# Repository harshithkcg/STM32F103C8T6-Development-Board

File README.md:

# STM32F103C8T6-Development-Board
Custom STM32F103C8T6 Development Board designed in KiCad with USB, SWD programming, UART, I2C and AMS1117 power supply.

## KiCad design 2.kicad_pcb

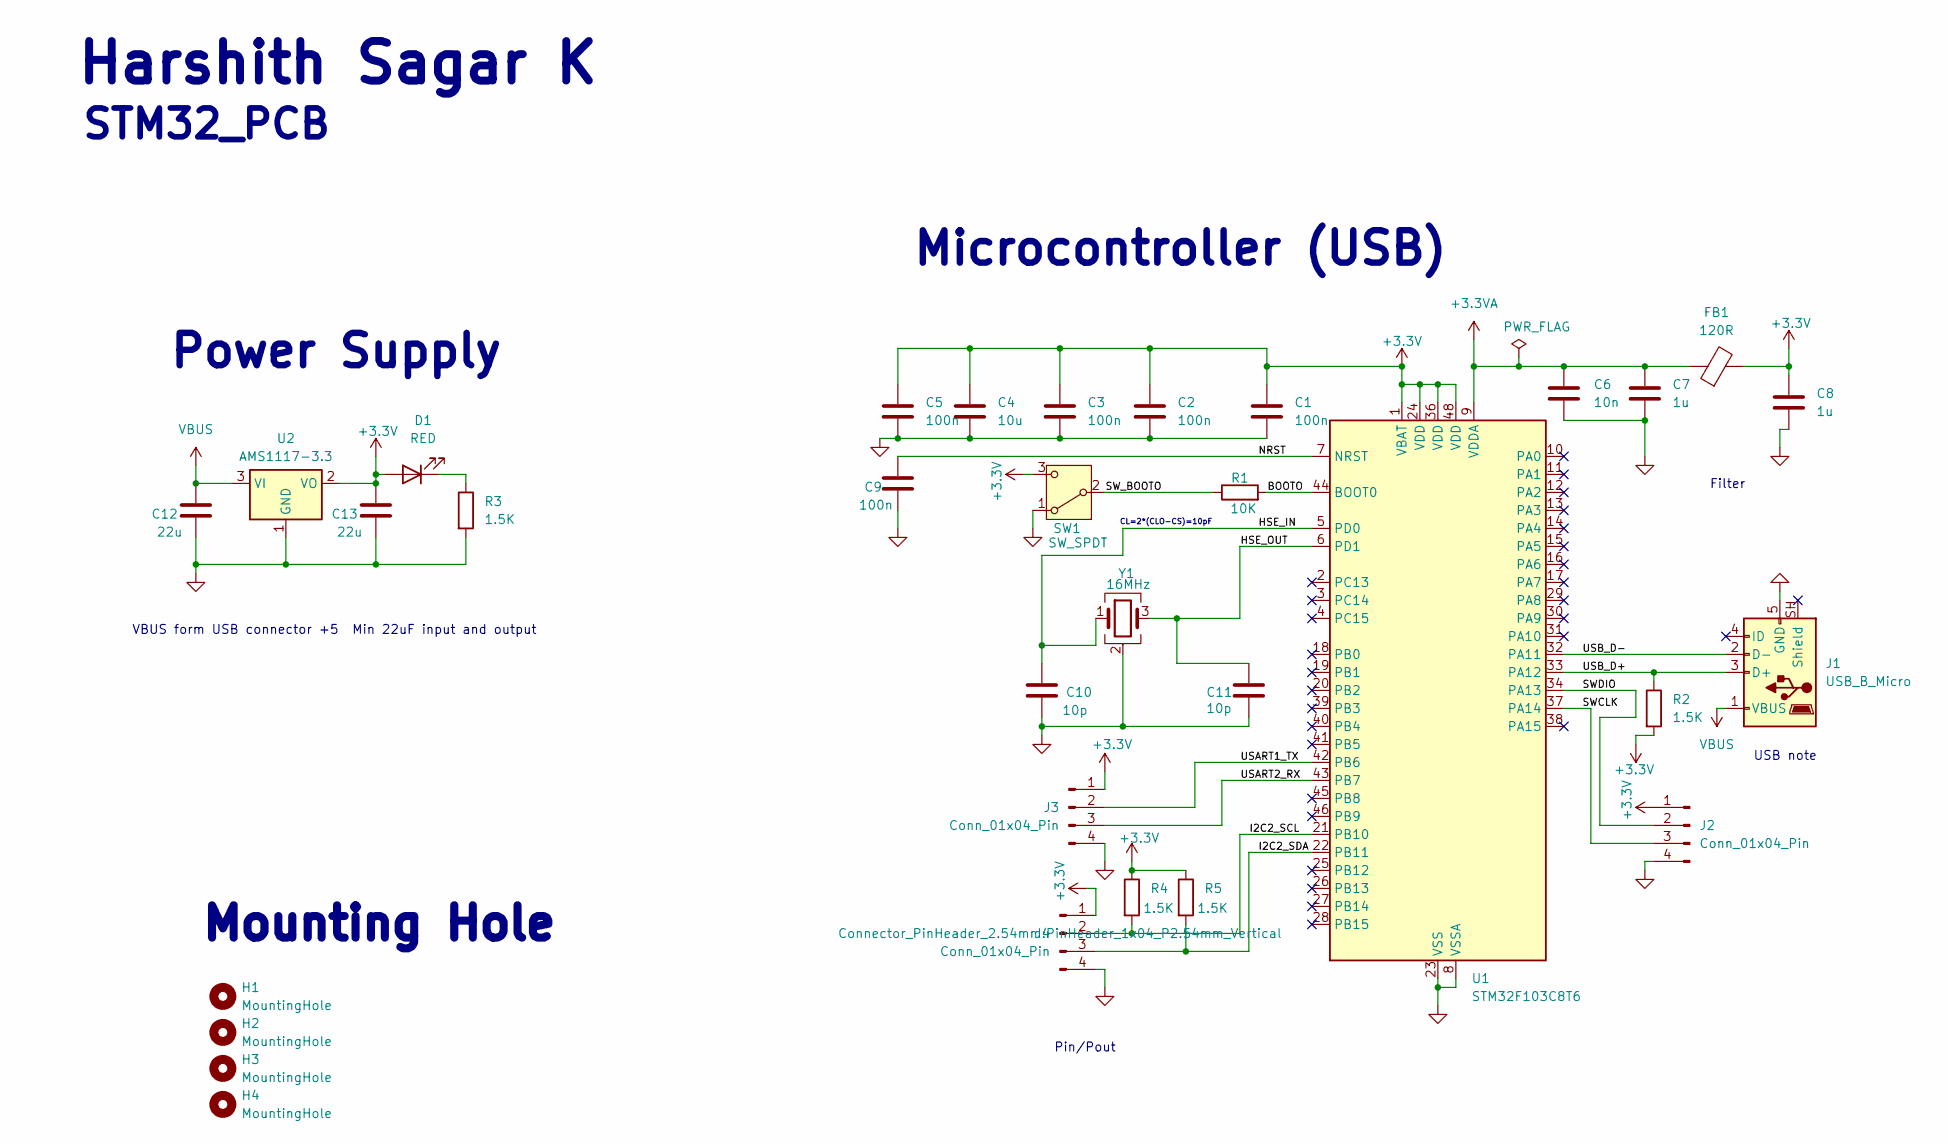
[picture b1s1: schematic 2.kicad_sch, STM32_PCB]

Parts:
C1, C2, C3, C5, C9: 100n; C_0402_1005Metric
C4: 10u; C_0603_1608Metric
C6: 10n; C_0402_1005Metric
C7, C8: 1u; C_0402_1005Metric
C10, C11: 10p; C_0402_1005Metric
C12, C13: 22u; C_0805_2012Metric
D1: RED; LED_0603_1608Metric
FB1: 120R; L_0603_1608Metric
H1, H2, H3, H4: MountingHole; MountingHole_2.1mm
J1: USB_B_Micro; USB_Micro-B_Wuerth_629105150521
J2, J3, J4: Conn_01x04_Pin; PinHeader_1x04_P2.54mm_Vertical
R1: 10K; R_0402_1005Metric
R2, R3, R4, R5: 1.5K; R_0402_1005Metric
SW1: SW_SPDT; SW_SPDT_PCM12
U1: STM32F103C8T6; LQFP-48_7x7mm_P0.5mm
U2: AMS1117-3.3; SOT-223-3_TabPin2
Y1: 16MHz; Crystal_SMD_3225-4Pin_3.2x2.5mm

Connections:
+3.3V: C1.1, C2.1, C3.1, C4.1, C5.1, C8.1, C13.1, D1.2 (A), FB1.2, J2.1, J3.1, J4.1, R2.2, R4.1, R5.1, SW1.3 (C), U1.1 (VBAT), U1.24 (VDD), U1.36 (VDD), U1.48 (VDD), U2.2 (VO)
+3.3VA: C6.1, C7.1, FB1.1, U1.9 (VDDA)
/BOOTO: R1.2, U1.44 (BOOT0)
/HSE_IN: C10.1, U1.5 (PD0), Y1.1
/HSE_OUT: C11.1, U1.6 (PD1), Y1.3
/I2C2_SCL: J4.2, R4.2, U1.21 (PB10)
/I2C2_SDA: J4.3, R5.2, U1.22 (PB11)
/NRST: C9.1, U1.7 (NRST)
/SWCLK: J2.3, U1.37 (PA14)
/SWDIO: J2.2, U1.34 (PA13)
/SW_BOOTO: R1.1, SW1.2 (B)
/USART1_TX: J3.2, U1.42 (PB6)
/USART2_RX: J3.3, U1.43 (PB7)
/USB_D+: J1.3 (D+), R2.1, U1.33 (PA12)
/USB_D-: J1.2 (D-), U1.32 (PA11)
GND: C1.2, C2.2, C3.2, C4.2, C5.2, C6.2, C7.2, C8.2, C9.2, C10.2, C11.2, C12.2, C13.2, J1.5 (GND), J2.4, J3.4, J4.4, R3.2, SW1.1 (A), U1.8 (VSSA), U1.23 (VSS), U1.35 (VSS), U1.47 (VSS), U2.1 (GND), Y1.2 (G), Y1.4 (G)
unnamed: D1.1 (K), R3.1
VBUS: C12.1, J1.1 (VBUS), U2.3 (VI)

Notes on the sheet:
Filter
STM32_PCB
VBUS form USB connector +5 Min 22uF input and output
Pin/Pout
Microcontroller (USB)
CL=2*(CLO-CS)=10pF
USB note
Power Supply
Mounting Hole
Harshith Sagar K

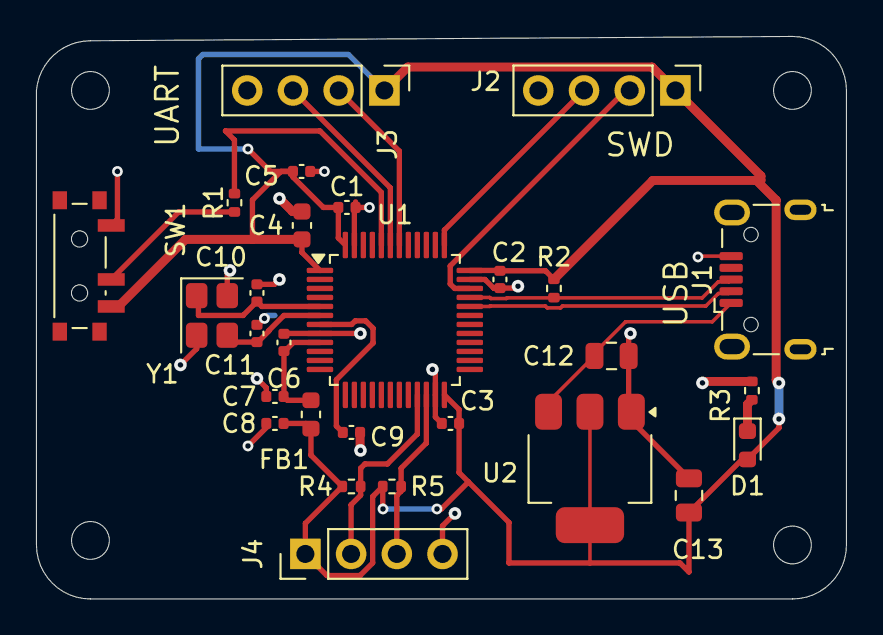
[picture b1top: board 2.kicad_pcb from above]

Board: 2 copper layers, 45.0 x 31.2 mm, 32 parts (0 on the bottom side), 18 nets.
